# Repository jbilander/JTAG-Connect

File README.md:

# JTAG-Connect
USB-blaster programming the intel/altera FPGA using a DIY spring clip with pogo-pins that clips onto a standard 2.0 mm pin pitch JTAG SMD-footprint:

<br />

<br />

***

video with the spring clip in action:<br />
https://drive.google.com/file/d/1q0D7EuQR9gsi54iwchI4ziomZzsiyqWE/view?usp=sharing

I have spare PCBs in case anyone is interested in this, or I can make to order for a fiver + shipping (until my spares are depleted) in case anyone can't build themselves. You will have to source the DIY clip (including screws) yourself from [aliexpress](https://www.aliexpress.com/item/1005004383076344.html) or similar.<br />
my email: jorgen.bilander at gmail com
<br />

The receptacle pogo pin socket I use, R50-3W:
https://www.aliexpress.com/item/1005003512878045.html

The pogo pin I use, P50-Q1:
https://www.aliexpress.com/item/1005002199072447.html

***
Connector pinout:

***

Designed for the common DIY spring clip plenty available on AliExpress:

***

The 6-pin handheld version:

</a>

***

A PCB panel also with a 6-pin version and handheld versions of the two:

***

When ordering from JLCPCB select:

Delivery Format: 

    Panel by Customer

Remove Order Number: 

    Specify a location

This will notify JLC where to put the order number, they will replace the "JLCJLCJLCJLC" silkscreen label.

And write a comment about V-scoring is specified on the User-Comment layer.

***

### Soldering the DIY clip PCBs:

<br />
Start with the back row (it will be easier to solder) and you can use a 2.0 mm pin pitch connector as a Jig to get the square top pins aligned.<br /> 

<br />

</a>

### Soldering the Handheld version:

I used a 2.0 mm pin pitch connector as a Jig to hold the pins in place at a nice consistent distance:

</a>

<br />

***

[![CC BY-SA 4.0][cc-by-sa-shield]][cc-by-sa]

This work is licensed under a
[Creative Commons Attribution-ShareAlike 4.0 International License][cc-by-sa].

[![CC BY-SA 4.0][cc-by-sa-image]][cc-by-sa]

[cc-by-sa]: http://creativecommons.org/licenses/by-sa/4.0/
[cc-by-sa-image]: https://licensebuttons.net/l/by-sa/4.0/88x31.png
[cc-by-sa-shield]: https://img.shields.io/badge/License-CC%20BY--SA%204.0-lightgrey.svg

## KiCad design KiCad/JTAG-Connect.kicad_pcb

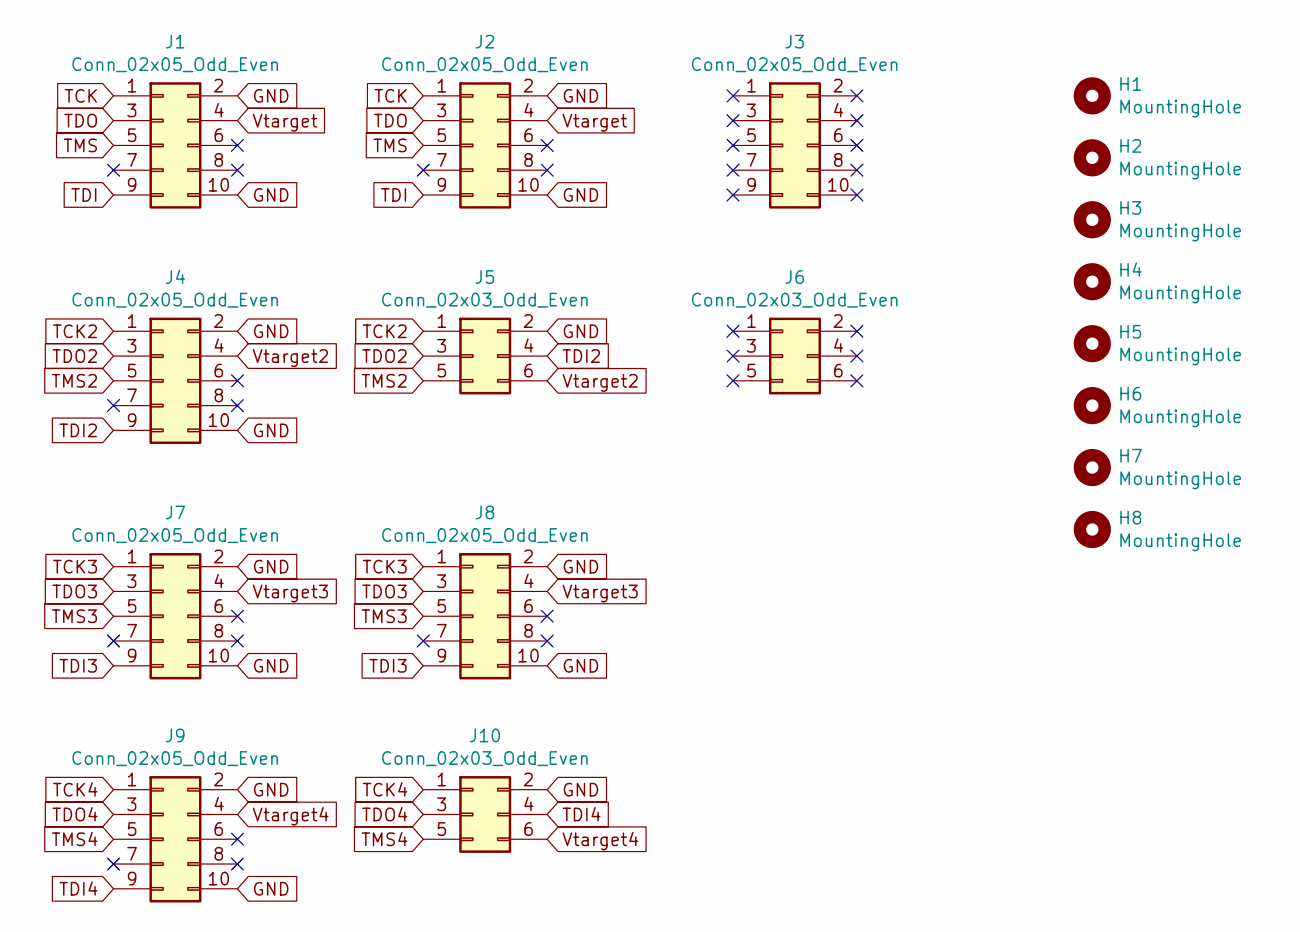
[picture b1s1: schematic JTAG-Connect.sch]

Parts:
H1, H2, H3, H4, H5, H6, H7, H8: MountingHole; MountingHole_2mm
J1, J4, J7, J9: Conn_02x05_Odd_Even; IDC-Header_2x05_P2.54mm_Vertical
J2, J3, J8: Conn_02x05_Odd_Even; PinHeader_2x05_P2.00mm_JTAG_connect_on_SMD_pads
J5, J6, J10: Conn_02x03_Odd_Even; PinHeader_2x03_P2.00mm_JTAG_connect_on_SMD_pads

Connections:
GND: J1.2, J1.10, J2.2, J2.10, J4.2, J4.10, J5.2, J7.2, J7.10, J8.2, J8.10, J9.2, J9.10, J10.2
TCK: J1.1, J2.1
TCK2: J4.1, J5.1
TCK3: J7.1, J8.1
TCK4: J9.1, J10.1
TDI: J1.9, J2.9
TDI2: J4.9, J5.4
TDI3: J7.9, J8.9
TDI4: J9.9, J10.4
TDO: J1.3, J2.3
TDO2: J4.3, J5.3
TDO3: J7.3, J8.3
TDO4: J9.3, J10.3
TMS: J1.5, J2.5
TMS2: J4.5, J5.5
TMS3: J7.5, J8.5
TMS4: J9.5, J10.5
Vtarget: J1.4, J2.4
Vtarget2: J4.4, J5.6
Vtarget3: J7.4, J8.4
Vtarget4: J9.4, J10.6

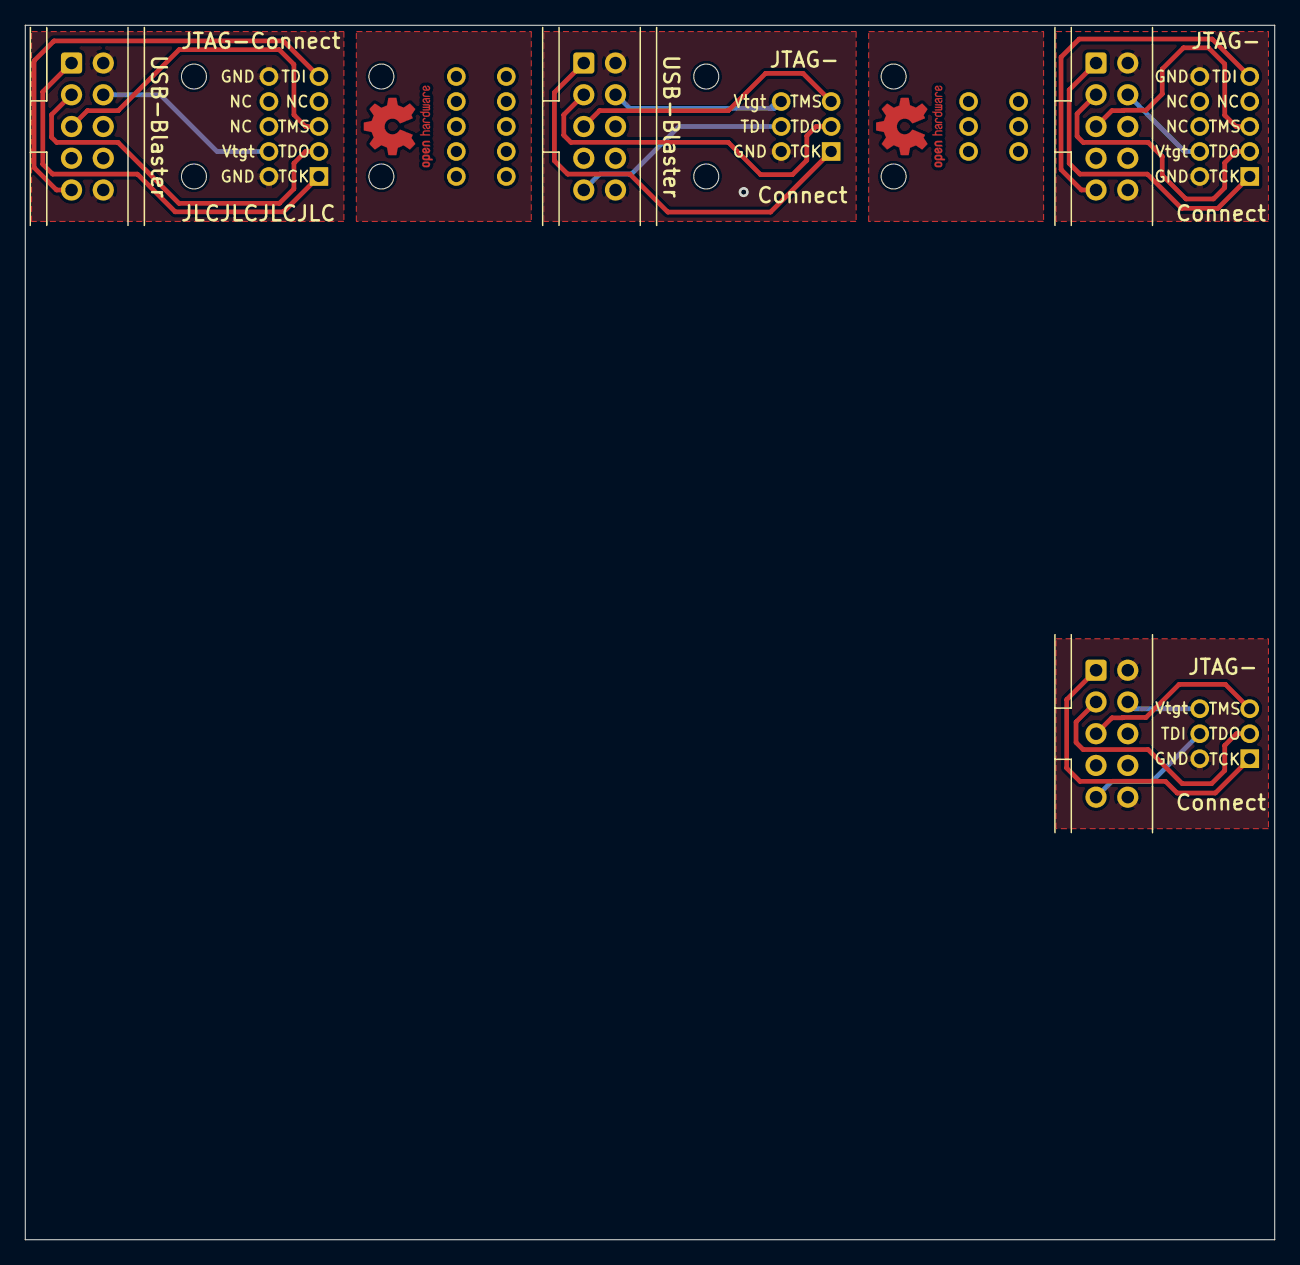
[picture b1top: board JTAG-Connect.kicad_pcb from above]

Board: 2 copper layers, 100.0 x 97.2 mm, 18 parts (0 on the bottom side), 21 nets.

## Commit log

2024-07-25 Add KiCad files
2024-07-28 Add footprints
2024-07-28 updated design
2024-07-30 Add file
2024-07-30 Increased OSHW-symbol text size
2024-08-08 Updated design to fit DIY spring clip.
2024-08-10 Add images
2024-08-10 Create LICENSE
2024-08-31 Add images of the 6-pin handheld version
2024-08-31 Add pic with connector pinout
2024-08-31 update pic
